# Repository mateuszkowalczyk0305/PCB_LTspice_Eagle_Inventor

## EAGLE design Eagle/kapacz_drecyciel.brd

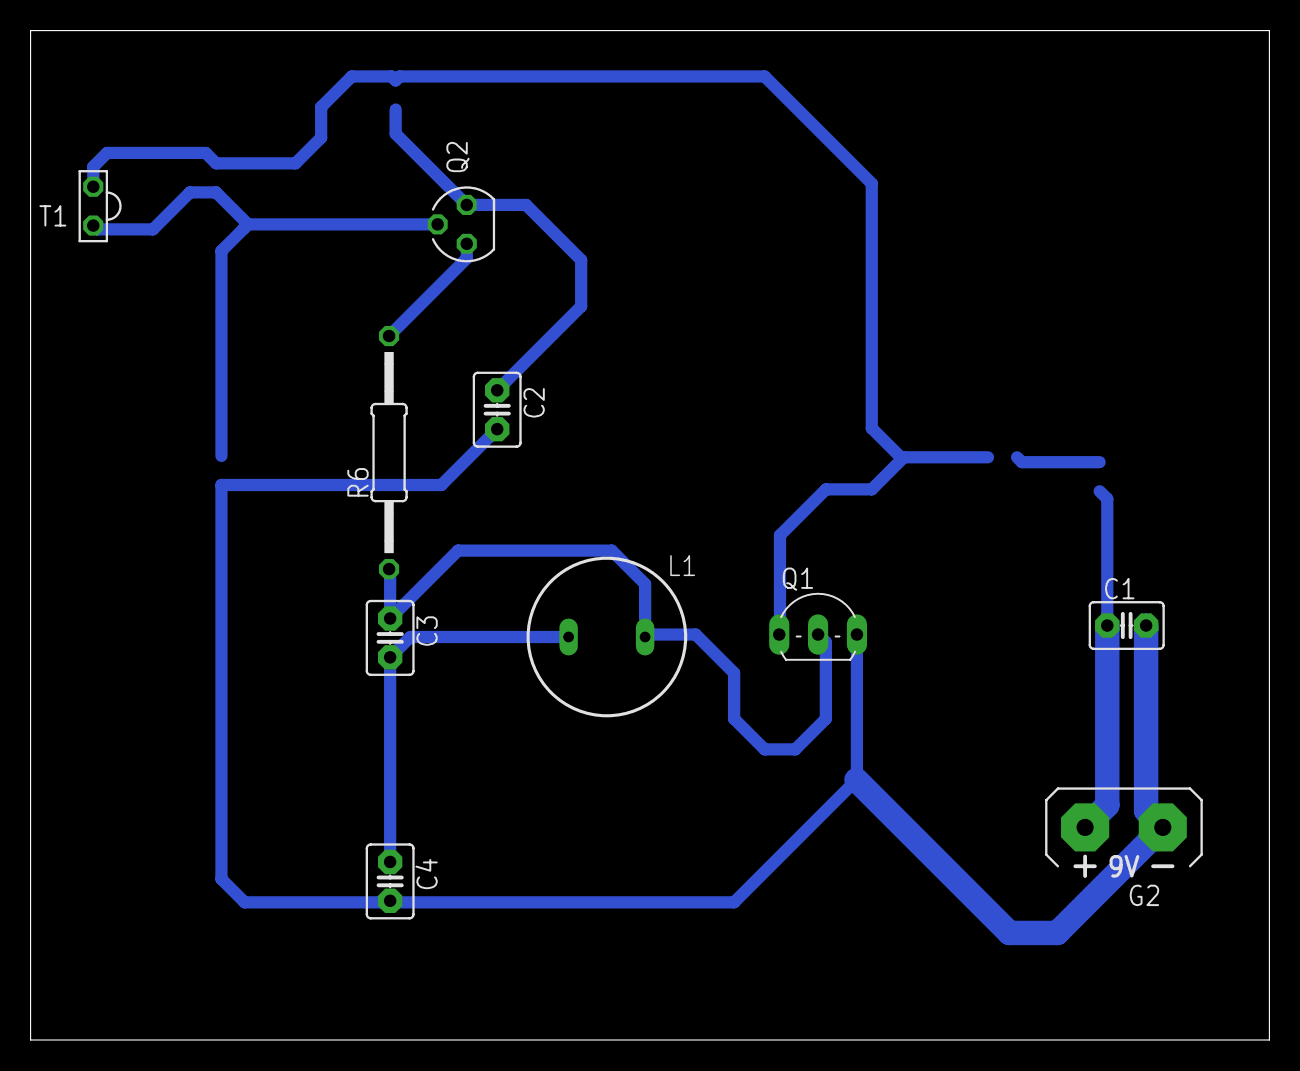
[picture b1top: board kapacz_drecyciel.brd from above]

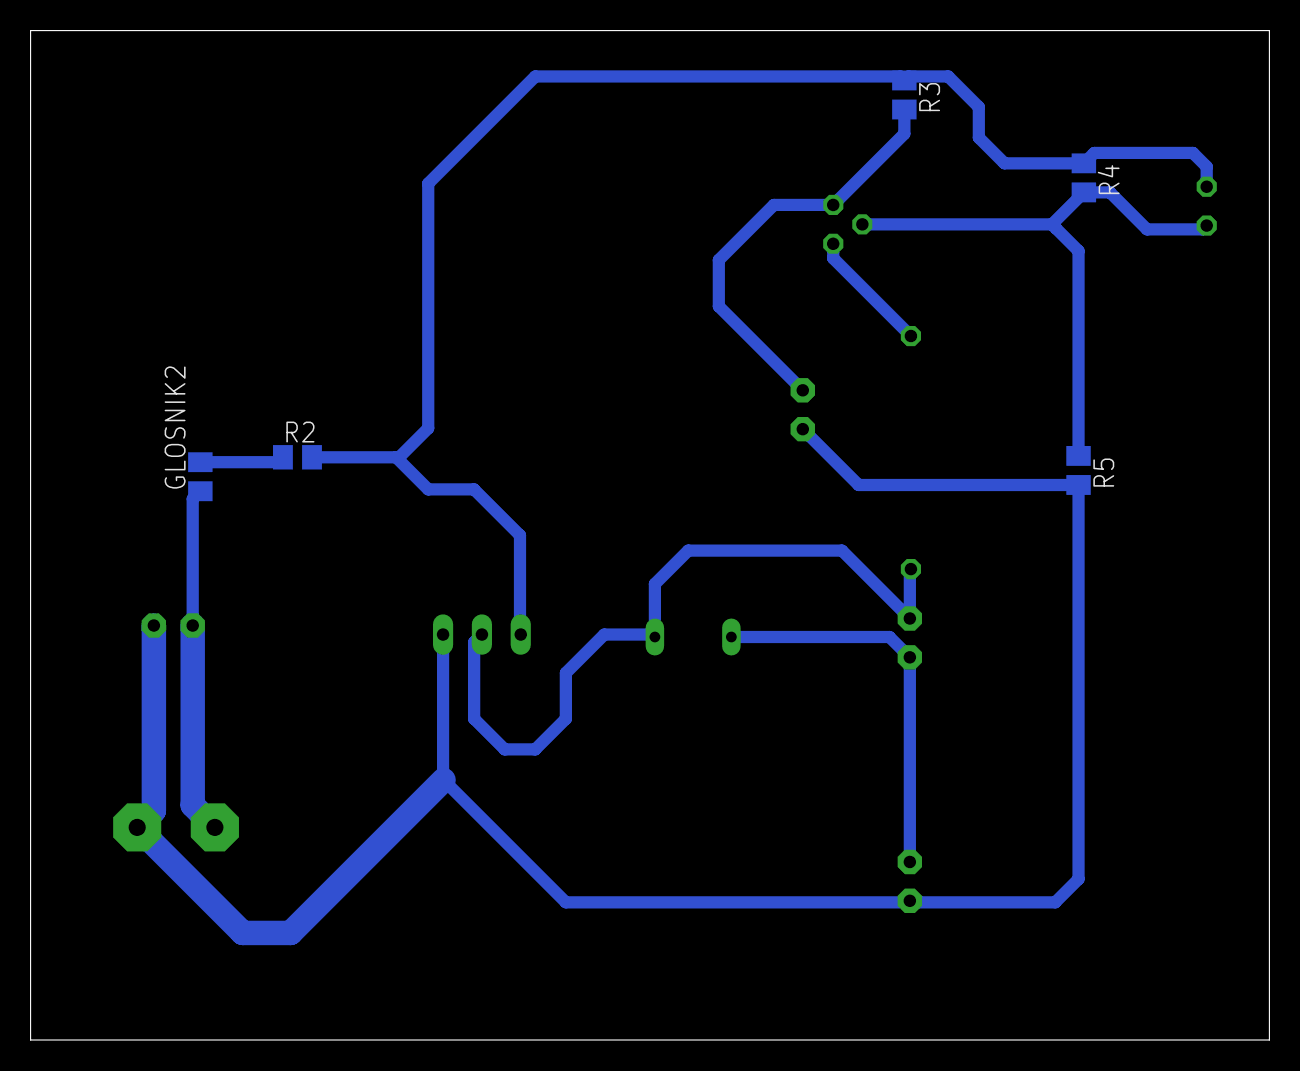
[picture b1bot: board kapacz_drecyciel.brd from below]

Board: 2 copper layers, 81.0 x 66.0 mm, 15 parts (5 on the bottom side), 9 nets.

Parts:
C1: 100u; C2.5-3
C2: 10u; C2.5-3
C3: 1u; C2.5-3
C4: 33u; C2.5-3
G2: AB9V
GLOSNIK2: 8; M0805
L1: 10mH; BS11
Q1: BC548; TO92-EBC
Q2: BC557; SOT54A
R2: 100; M0805
R3: 470k; M0805
R4, R5: 1M; M0805
R6: 3k; 0207/15
T1: LPT80A

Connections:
GND: C1.2, C2.2, C4.2, G2.-, Q1.E, R5.2
unnamed: C1.1, G2.+, GLOSNIK2.1
unnamed: Q2.C, R6.2
unnamed: C3.1, L1.2, Q1.B, R6.1
unnamed: C3.2, C4.1, L1.1
unnamed: C2.1, Q2.E, R3.2
unnamed: GLOSNIK2.2, R2.1
unnamed: Q2.B, R4.2, R5.1, T1.E
unnamed: Q1.C, R2.2, R3.1, R4.1, T1.C

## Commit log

2024-03-28 Kapacz dreczyciel
